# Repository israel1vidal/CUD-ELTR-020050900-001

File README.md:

# Olimpiadas nacionales 2022
Inversor dedicado a estación de servicios de telecomunicaciones ubicado en la provincia de Neuquén.

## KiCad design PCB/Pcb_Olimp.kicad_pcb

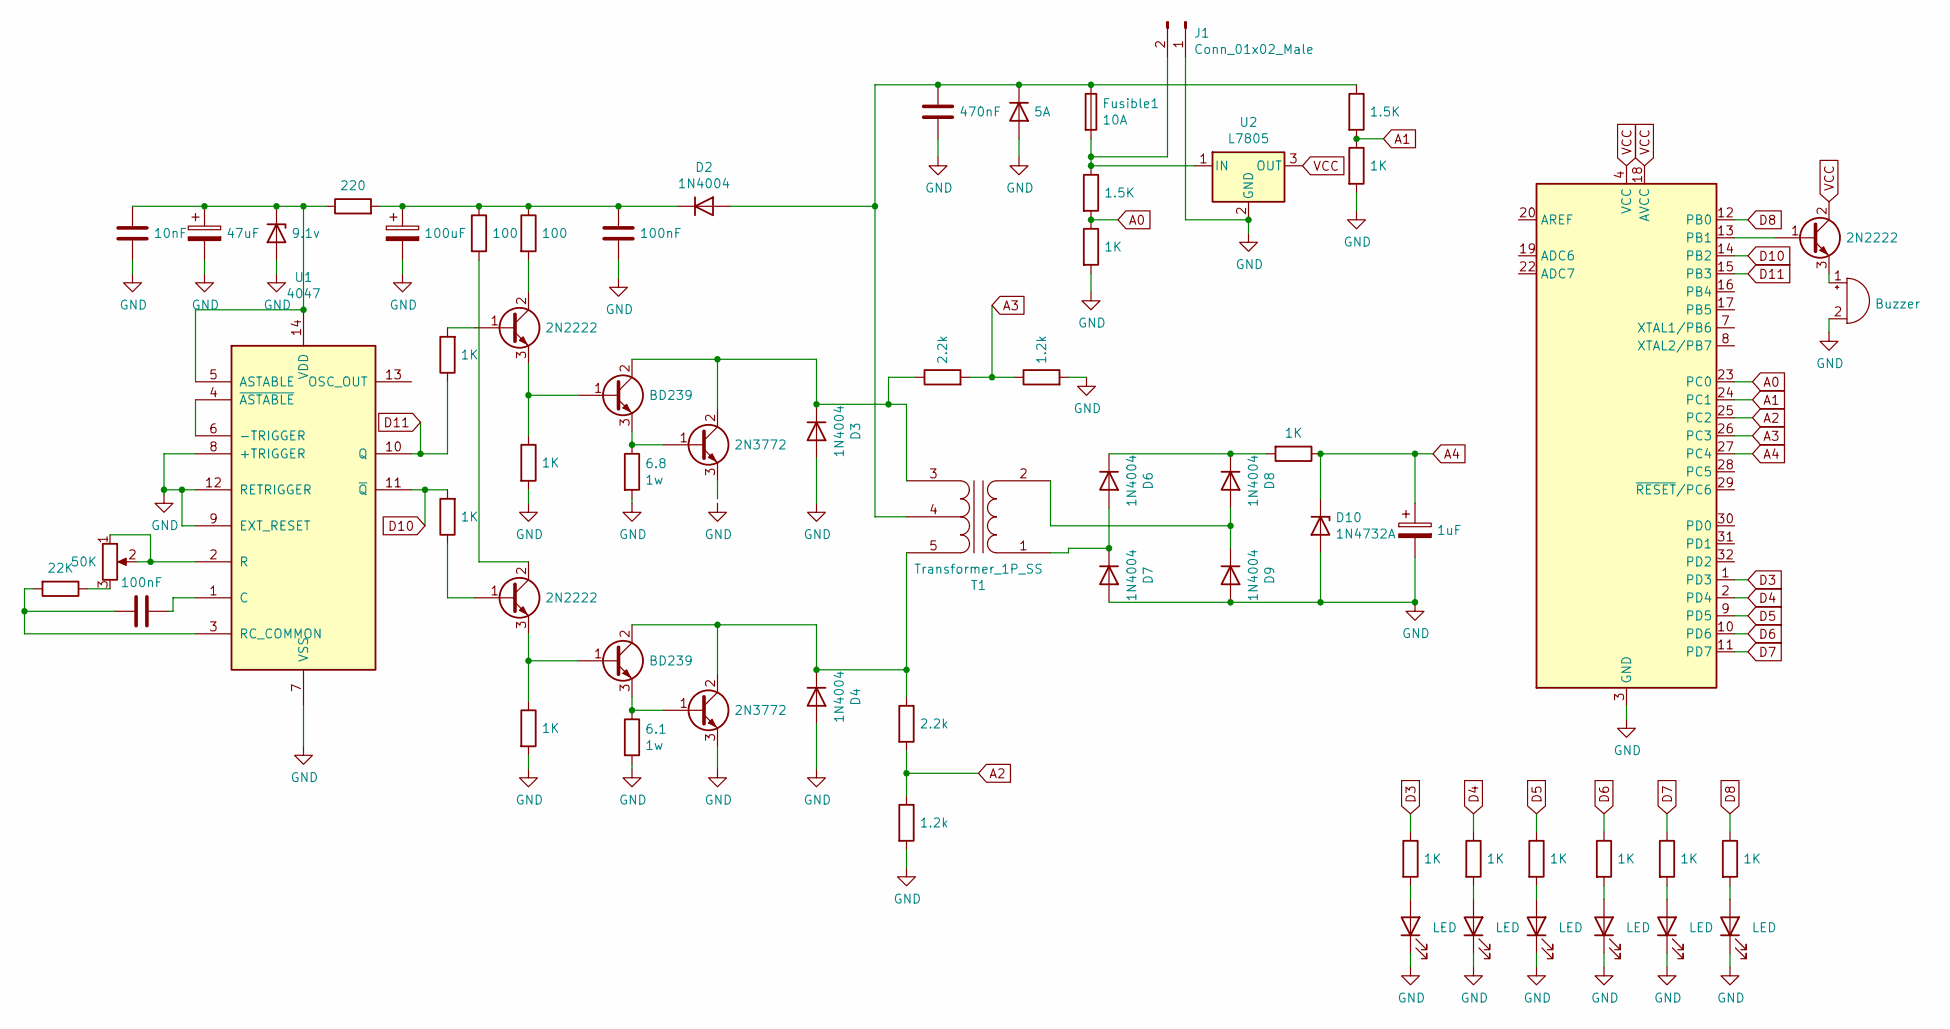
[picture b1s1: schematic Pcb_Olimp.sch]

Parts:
6.1: 1w; R_Axial_Power_L20.0mm_W6.4mm_P25.40mm
6.8: 1w; R_Axial_DIN0617_L17.0mm_D6.0mm_P5.08mm_Vertical
6u1: 22K; R_0805_2012Metric
6u2: 100; R_0805_2012Metric
BZ1: Buzzer; Buzzer_15x7.5RM7.6
C1: 10nF; C_0805_2012Metric
C2: 100nF; C_0805_2012Metric
C3: 47uF; CP_Elec_5x5.7
C4: 100uF; CP_Elec_5x5.7
C5: 470nF; C_0805_2012Metric
C6: 1uF; CP_Elec_5x5.9
D1: 9.1v; D_DO-41_SOD81_P10.16mm_Horizontal
D2, D3, D4, D6, D7, D8, D9: 1N4004; D_DO-41_SOD81_P10.16mm_Horizontal
D5: 5A; D_DO-41_SOD81_P10.16mm_Horizontal
D10: 1N4732A; D_DO-41_SOD81_P10.16mm_Horizontal
D11, D12, D13, D14, D15, D16: LED; LED_D4.0mm
Fusible1: 10A; Fuse_Bourns_MF-RG900
J1: Conn_01x02_Male; TerminalBlock_Altech_AK300-2_P5.00mm
Q1, Q2, Q7: 2N2222; TO-18-3
Q3, Q4: BD239; TO-220-3_Vertical
Q5, Q6: 2N3772; NEC_Molded_7x4x9mm
R1: 220; R_0805_2012Metric
R2, R3, R5, R6, R12, R13, R15, R16, R17, R18, R19, R20, R21: 1K; R_0805_2012Metric
R4: 100; R_0805_2012Metric
R7, R9: 2.2k; R_0805_2012Metric
R8, R10: 1.2k; R_0805_2012Metric
R11, R14: 1.5K; R_0805_2012Metric
RV1: 50K; Potentiometer_Alps_RK09K_Single_Horizontal
T1: Transformer_1P_SS; TerminalBlock_bornier-5_P5.08mm
U1: 4047; DIP-16_W7.62mm
U2: L7805; TO-220-3_Vertical
U3: ATmega328P-AU; TQFP-32_7x7mm_P0.8mm
c1: 100nF; C_0805_2012Metric

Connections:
A0: R11.2, R12.1, U3.23 (PC0)
A1: R14.2, R15.1, U3.24 (PC1)
A2: R7.2, R8.1, U3.25 (PC2)
A3: R9.2, R10.1, U3.26 (PC3)
A4: C6.1, D10.1 (K), R13.1, U3.27 (PC4)
D3: R16.1, U3.1 (PD3)
D4: R17.1, U3.2 (PD4)
D5: R18.1, U3.9 (PD5)
D6: R19.1, U3.10 (PD6)
D7: R20.1, U3.11 (PD7)
D8: R21.1, U3.12 (PB0)
D10: R3.2, U1.11 (~Q), U3.14 (PB2)
D11: R2.1, U1.10 (Q), U3.15 (PB3)
GND: 6.1.2, 6.8.2, BZ1.2 (+), C1.2, C3.2, C4.2, C5.2, C6.2, D1.2 (A), D3.2 (A), D4.2 (A), D5.2 (A), D7.2 (A), D9.2 (A), D10.2 (A), D11.1 (K), D12.1 (K), D13.1 (K), D14.1 (K), D15.1 (K), D16.1 (K), J1.1, Q6.3 (E), R5.2, R6.2, R8.2, R10.2, R12.2, R15.2, U1.7 (VSS), U1.8 (+TRIGGER), U1.9 (EXT_RESET), U1.12 (RETRIGGER), U2.2 (GND), U3.3 (GND), U3.5 (GND), U3.21 (GND), c1.2
unnamed: 6.1.1, Q4.3 (E), Q6.1 (B)
unnamed: 6.8.1, Q3.3 (E), Q5.1 (B)
unnamed: 6u1.1, RV1.3
unnamed: 6u1.2, C2.1, U1.3 (RC_COMMON)
unnamed: 6u2.1, C4.1, D2.1 (K), R1.2, R4.1, c1.1
unnamed: 6u2.2, Q2.2 (C)
unnamed: BZ1.1 (-), Q7.3 (E)
unnamed: C1.1, C3.1, D1.1 (K), R1.1, U1.5 (ASTABLE), U1.14 (VDD)
unnamed: C2.2, U1.1 (C)
unnamed: C5.1, D2.2 (A), D5.1 (K), Fusible1.1, R14.1, T1.4 (SC)
unnamed: D3.1 (K), Q3.2 (C), Q5.2 (C), R9.1, T1.3 (SA)
unnamed: D4.1 (K), Q4.2 (C), Q6.2 (C), R7.1, T1.5 (SB)
unnamed: D6.1 (K), D8.1 (K), R13.2
unnamed: D6.2 (A), D7.1 (K), T1.1 (AA)
unnamed: D8.2 (A), D9.1 (K), T1.2 (AB)
unnamed: D11.2 (A), R16.2
unnamed: D12.2 (A), R17.2
unnamed: D13.2 (A), R18.2
unnamed: D14.2 (A), R19.2
unnamed: D15.2 (A), R20.2
unnamed: D16.2 (A), R21.2
unnamed: Fusible1.2, J1.2, R11.1, U2.1 (IN)
unnamed: Q1.1 (B), R2.2
unnamed: Q1.2 (C), R4.2
unnamed: Q1.3 (E), Q3.1 (B), R5.1
unnamed: Q2.1 (B), R3.1
unnamed: Q2.3 (E), Q4.1 (B), R6.1
unnamed: Q7.1 (B), U3.13 (PB1)
unnamed: RV1.1, RV1.2, U1.2 (R)
unnamed: U1.4 (~ASTABLE), U1.6 (-TRIGGER)
VCC: Q7.2 (C), U2.3 (OUT), U3.4 (VCC), U3.6 (VCC), U3.18 (AVCC)

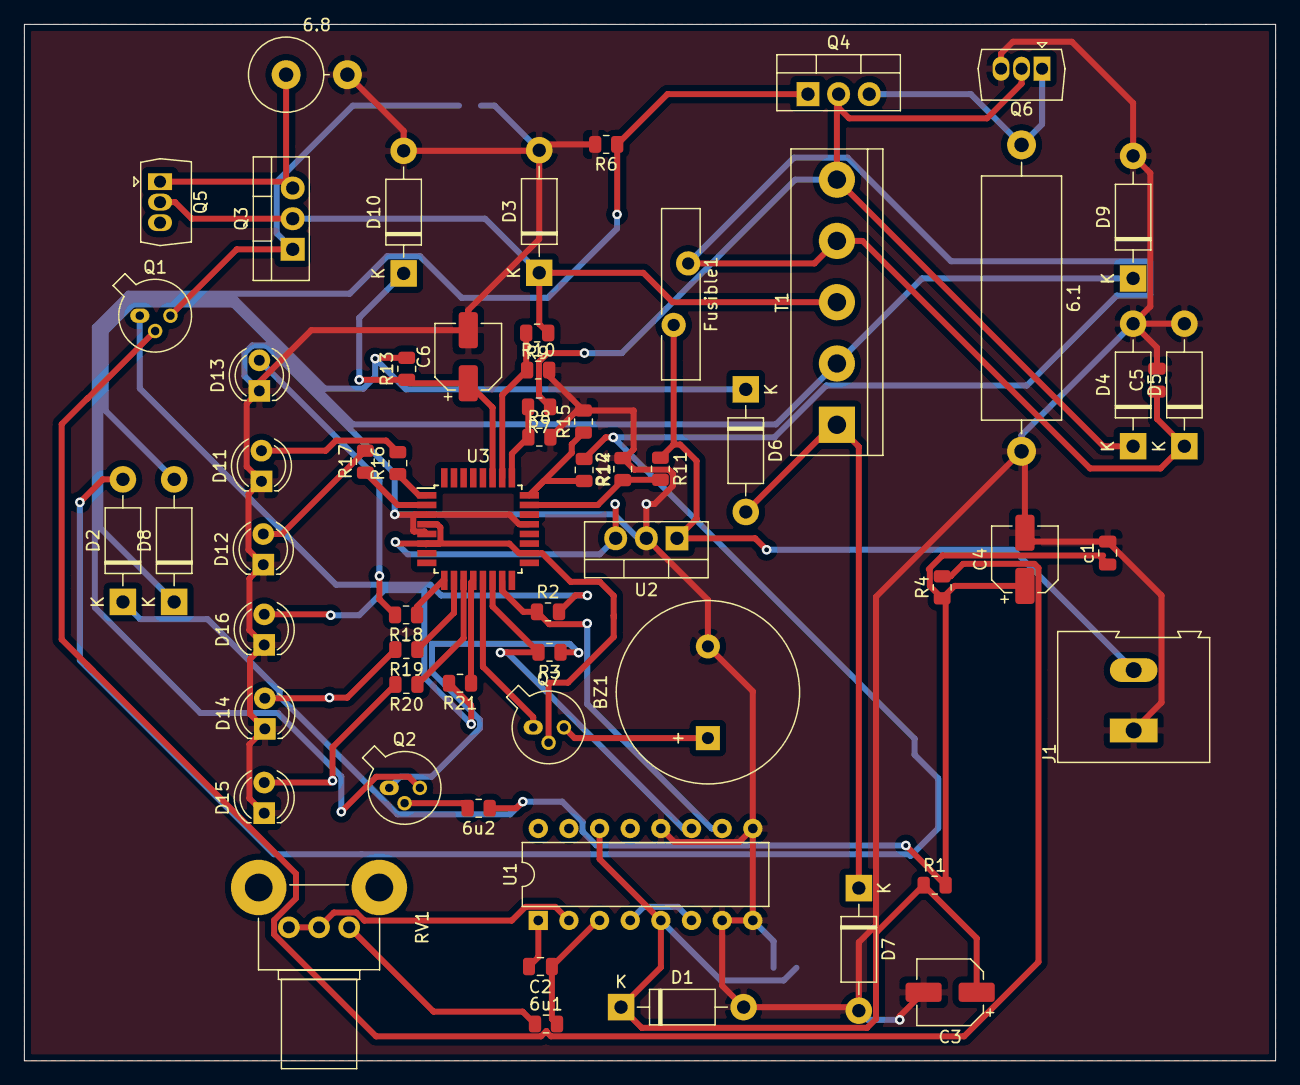
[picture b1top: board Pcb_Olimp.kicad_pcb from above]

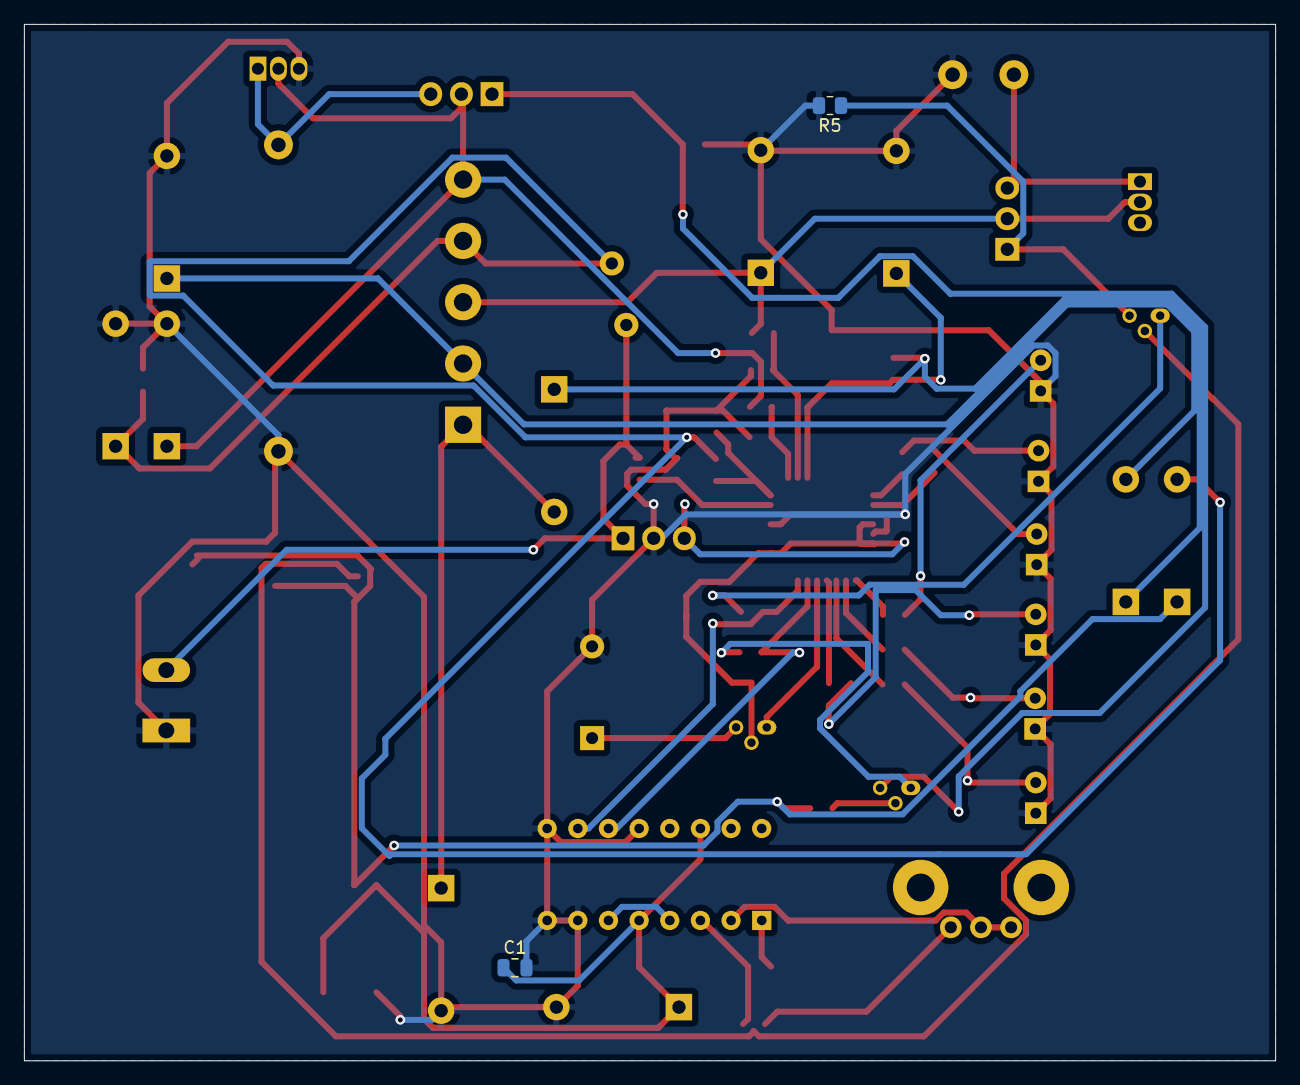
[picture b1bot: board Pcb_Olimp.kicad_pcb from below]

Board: 2 copper layers, 103.7 x 85.9 mm, 63 parts (2 on the bottom side), 45 nets.

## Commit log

2022-11-17 Rename Read.me to README.md
2022-11-17 Rename README.dm to README.md
2022-11-17 Create PCB
2022-11-18 Create Software de testeo ESP8266
2022-11-18 Create Software del Sistema de Detección de Errores
2022-11-18 Rename Software del Sistema de Detección de Errores to Software del Sistema de Detección de Errores.c
